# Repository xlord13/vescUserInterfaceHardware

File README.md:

# User interface board for VESC controller on e-twow scooter

This user interface board is based on an stm32F4 microcontroler.
The hardware design has been optimized for e-twow scooters, but can be adapted to any electric engine.
Is has been made with KiCad, which is a cross platform and open source electronics design automation suite.

This board communicates with a VESC controller by a UART interface.
It has 4 buttons and a color OLED 128x128 display (SSD1351) for user interaction.
Additionnaly, it includes 6 leds and a photo resistor for automatic lighting when ambient lighting is too low.

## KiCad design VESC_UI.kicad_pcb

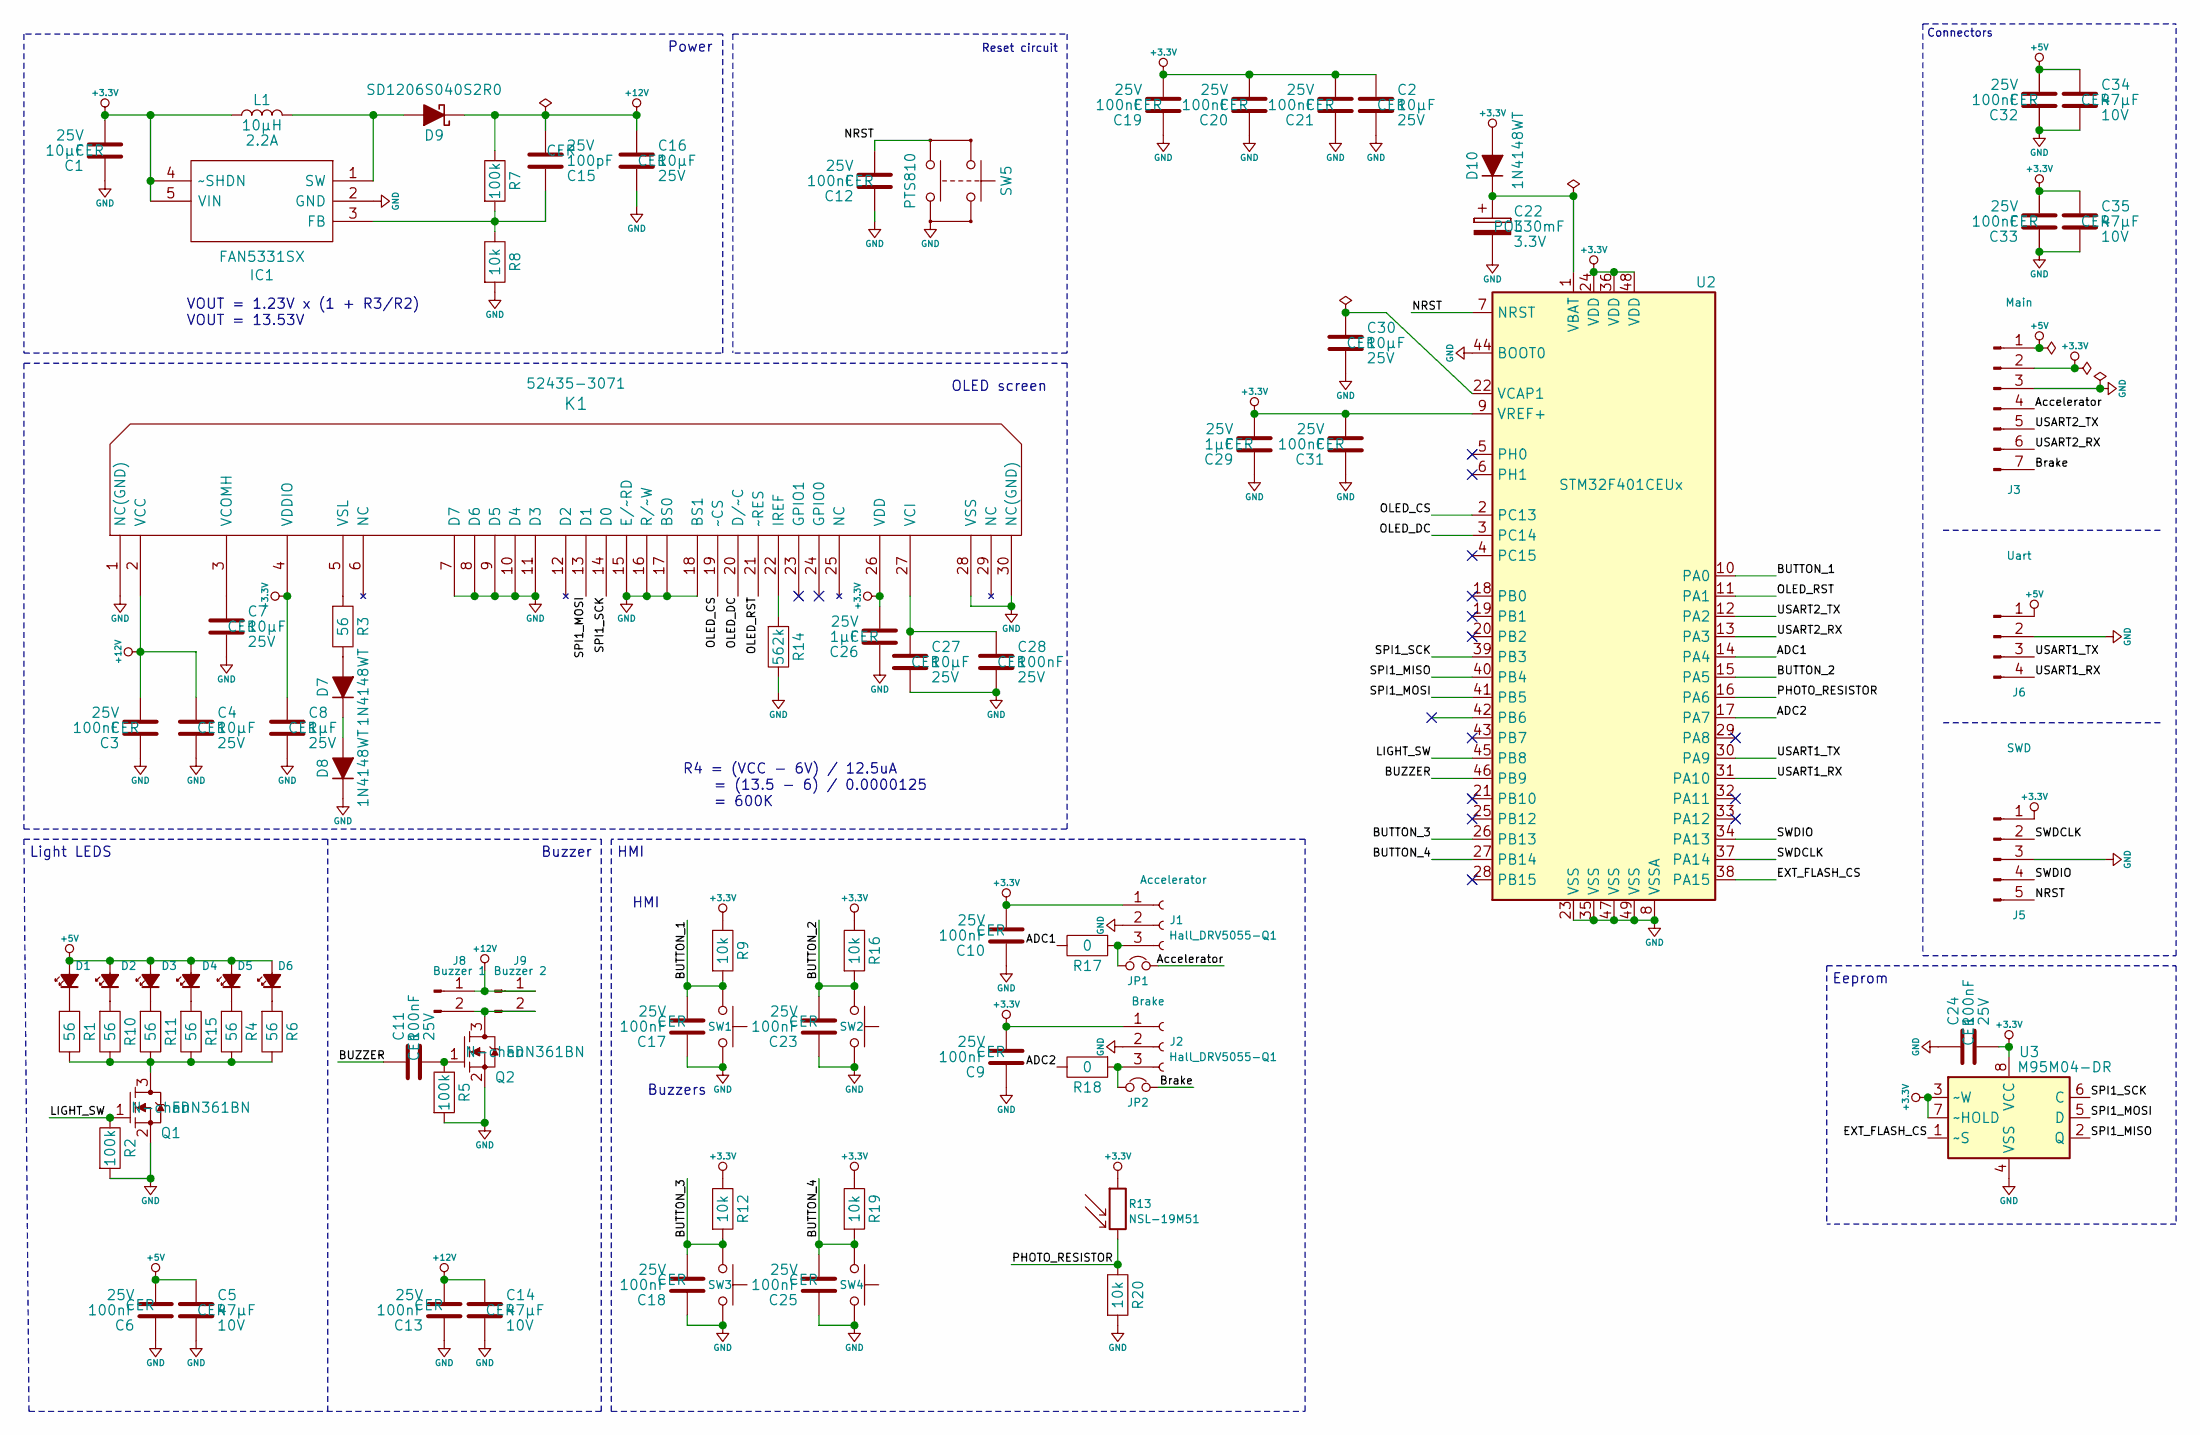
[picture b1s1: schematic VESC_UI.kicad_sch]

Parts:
C1, C2, C4, C7, C16, C27, C30: C_0003; C_0603
C3, C6, C9, C10, C11, C12, C13, C17, C18, C19, C20, C21, C23, C24, C25, C28, C31, C32, C33: C_0002; C_0402
C5, C14, C34, C35: C_0040; C_1210
C8, C26, C29: C_0037; C_0603
C15: C_0051; C_0402
C22: C_0046; CP_ELNA-DSK621
D1, D2, D3, D4, D5, D6: LED 5mm - White; LED_D5.0mm_Horizontal_O1.27mm_Z3.0mm_Clear
D7, D8, D10: D_0022; D_SOD-523-F
D9: D_0016; D_SOD-123
IC1: FAN5331SX; SOT95P280X145-5N; Mouser Part Number 512-FAN5331SX
J1, J2: Hall_DRV5055-Q1; TO-92Flat
J3: Conn_01x07_Male; JST_PH_B7B-PH-K_1x07_P2.00mm_Vertical
J5: Conn_01x05_Male; JST_PH_B5B-PH-K_1x05_P2.00mm_Vertical
J6: Conn_01x04_Male; JST_PH_B4B-PH-K_1x04_P2.00mm_Vertical
J8, J9: Conn_01x02_Male; JST_PH_B2B-PH-K_1x02_P2.00mm_Vertical
JP1, JP2: Jumper_NC_Small; SolderJumper-2_P1.3mm_Open_TrianglePad1.0x1.5mm
K1: K_0051-OBSOLETE; OLED128x128-1P5
L1: L_0006; L_4012-Wurth
Q1, Q2: Q_0020; SOT_23
R1, R4, R6, R10, R11, R15: R_0110; R_0603
R2, R5, R7: R_0034; R_0402
R3: R_0110; R_0402
R8, R9, R12, R16, R19, R20: R_0020; R_0402
R13: NSL-19M51; R_LDR_4.9x4.2mm_P2.54mm_Vertical
R14: R_0019; R_0402
R17, R18: R_0001; R_0402
SW1, SW2, SW3, SW4: Vertical push button; Vertical_push_button
SW5: SW_0003; PTS810
U2: STM32F401CEUx; QFN-48-1EP_7x7mm_P0.5mm_EP5.6x5.6mm
U3: M95M04-DR; SOIC-8_3.9x4.9mm_P1.27mm

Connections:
+3.3V: C1.2, C2.1, C8.1, C9.2, C10.2, C19.2, C20.2, C21.2, C24.2, C26.2, C29.2, C31.2, C33.2, C35.1, D10.2 (A), IC1.4 (~SHDN), IC1.5 (VIN), J1.1, J2.1, J3.2, J5.1, K1.4 (VDDIO), K1.26 (VDD), L1.2, R9.2, R12.2, R13.1, R16.2, R19.2, U2.9 (VREF+), U2.24 (VDD), U2.36 (VDD), U2.48 (VDD), U3.3 (~W), U3.7 (~HOLD), U3.8 (VCC)
+5V: C5.1, C6.2, C32.2, C34.1, D1.2 (A), D2.2 (A), D3.2 (A), D4.2 (A), D5.2 (A), D6.2 (A), J3.1, J6.1
+12V: C3.2, C4.1, C13.2, C14.1, C15.2, C16.1, D9.1 (K), J8.1, J9.1, K1.2 (VCC), R7.2
/ADC1: R17.2, U2.14 (PA4)
/ADC2: R18.2, U2.17 (PA7)
/Accelerator: J3.4, JP1.2
/BUTTON_1: C17.2, R9.1, SW1.1, U2.10 (PA0)
/BUTTON_2: C23.2, R16.1, SW2.1, U2.15 (PA5)
/BUTTON_3: C18.2, R12.1, SW3.1, U2.26 (PB13)
/BUTTON_4: C25.2, R19.1, SW4.1, U2.27 (PB14)
/BUZZER: C11.1, U2.46 (PB9)
/Brake: J3.7, JP2.2
/EXT_FLASH_CS: U2.38 (PA15), U3.1 (~S)
/LIGHT_SW: Q1.1 (G), R2.2, U2.45 (PB8)
/NRST: C12.2, J5.5, SW5.2, U2.7 (NRST)
/OLED_CS: K1.19 (~CS), U2.2 (PC13)
/OLED_DC: K1.20 (D/~C), U2.3 (PC14)
/OLED_RST: K1.21 (~RES), U2.11 (PA1)
/PHOTO_RESISTOR: R13.2, R20.2, U2.16 (PA6)
/SPI1_MISO: U2.40 (PB4), U3.2 (Q)
/SPI1_MOSI: K1.13 (D1), U2.41 (PB5), U3.5 (D)
/SPI1_SCK: K1.14 (D0), U2.39 (PB3), U3.6 (C)
/SWDCLK: J5.2, U2.37 (PA14)
/SWDIO: J5.4, U2.34 (PA13)
/USART1_RX: J6.4, U2.31 (PA10)
/USART1_TX: J6.3, U2.30 (PA9)
/USART2_RX: J3.6, U2.13 (PA3)
/USART2_TX: J3.5, U2.12 (PA2)
GND: C1.1, C2.2, C3.1, C4.2, C5.2, C6.1, C7.2, C8.2, C9.1, C10.1, C12.1, C13.1, C14.2, C16.2, C17.1, C18.1, C19.1, C20.1, C21.1, C22.2, C23.1, C24.1, C25.1, C26.1, C27.2, C28.2, C29.1, C30.2, C31.1, C32.1, C33.1, C34.2, C35.2, D8.1 (K), IC1.2 (GND), J1.2, J2.2, J3.3, J5.3, J6.2, K1.1 (NC(GND)), K1.7 (D7), K1.8 (D6), K1.9 (D5), K1.10 (D4), K1.11 (D3), K1.15 (E/~RD), K1.16 (R/~W), K1.17 (BS0), K1.18 (BS1), K1.28 (VSS), K1.30 (NC(GND)), Q1.2 (S), Q2.2 (S), R2.1, R5.1, R8.1, R14.2, R20.1, SW1.2, SW2.2, SW3.2, SW4.2, SW5.3, U2.8 (VSSA), U2.23 (VSS), U2.35 (VSS), U2.44 (BOOT0), U2.47 (VSS), U2.49 (VSS), U3.4 (VSS)
unnamed: C7.1, K1.3 (VCOMH)
unnamed: C11.2, Q2.1 (G), R5.2
unnamed: C15.1, IC1.3 (FB), R7.1, R8.2
unnamed: C22.1, D10.1 (K), U2.1 (VBAT)
unnamed: C27.1, C28.1, K1.27 (VCI)
unnamed: C30.1, U2.22 (VCAP1)
unnamed: D1.1 (K), R1.1
unnamed: D2.1 (K), R10.1
unnamed: D3.1 (K), R11.1
unnamed: D4.1 (K), R15.1
unnamed: D5.1 (K), R4.1
unnamed: D6.1 (K), R6.1
unnamed: D7.1 (K), D8.2 (A)
unnamed: D7.2 (A), R3.2
unnamed: D9.2 (A), IC1.1 (SW), L1.1
unnamed: J1.3, JP1.1, R17.1
unnamed: J2.3, JP2.1, R18.1
unnamed: J8.2, J9.2, Q2.3 (D)
unnamed: K1.5 (VSL), R3.1
unnamed: K1.22 (IREF), R14.1
unnamed: Q1.3 (D), R1.2, R4.2, R6.2, R10.2, R11.2, R15.2

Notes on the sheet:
Buzzer
HMI
Eeprom
Buzzers
Light LEDS
R4 = (VCC - 6V) / 12.5uA = (13.5 - 6) / 0.0000125 = 600K
Power
Connectors
Reset circuit
OLED screen
VOUT = 1.23V x (1 + R3/R2) VOUT = 13.53V

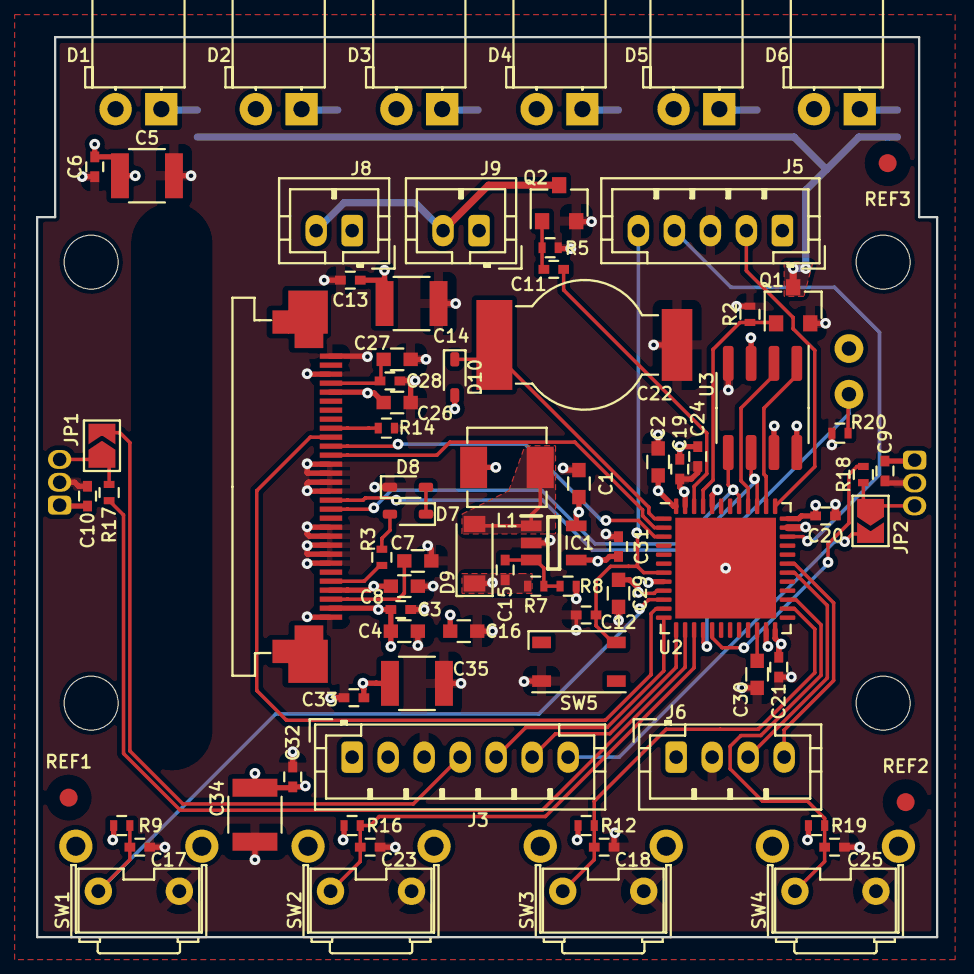
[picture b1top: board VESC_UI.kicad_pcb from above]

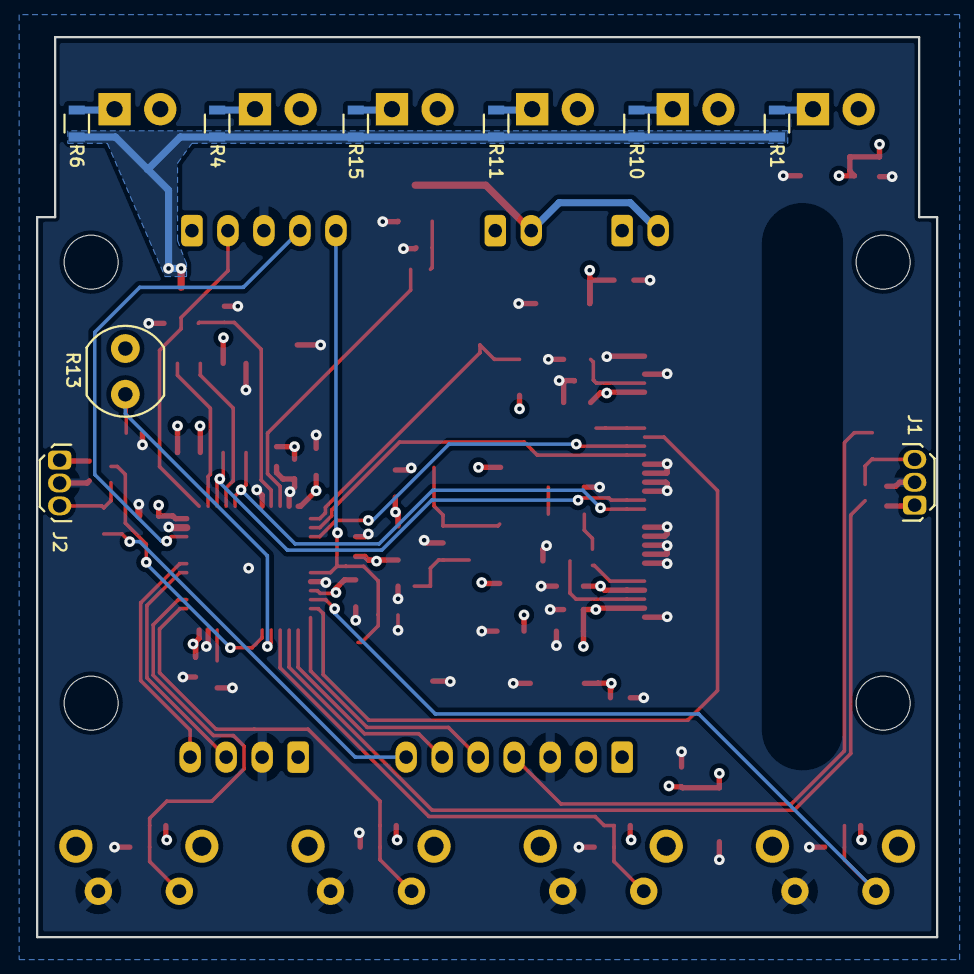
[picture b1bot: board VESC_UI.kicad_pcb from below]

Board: 4 copper layers, 50.0 x 50.0 mm, 93 parts (9 on the bottom side), 50 nets.

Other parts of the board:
Hole1, Hole2, Hole3, Hole4: MountingHole_3.2mm_M3_DIN965
REF1, REF2, REF3: CircleWhite1mm; REF_1mm

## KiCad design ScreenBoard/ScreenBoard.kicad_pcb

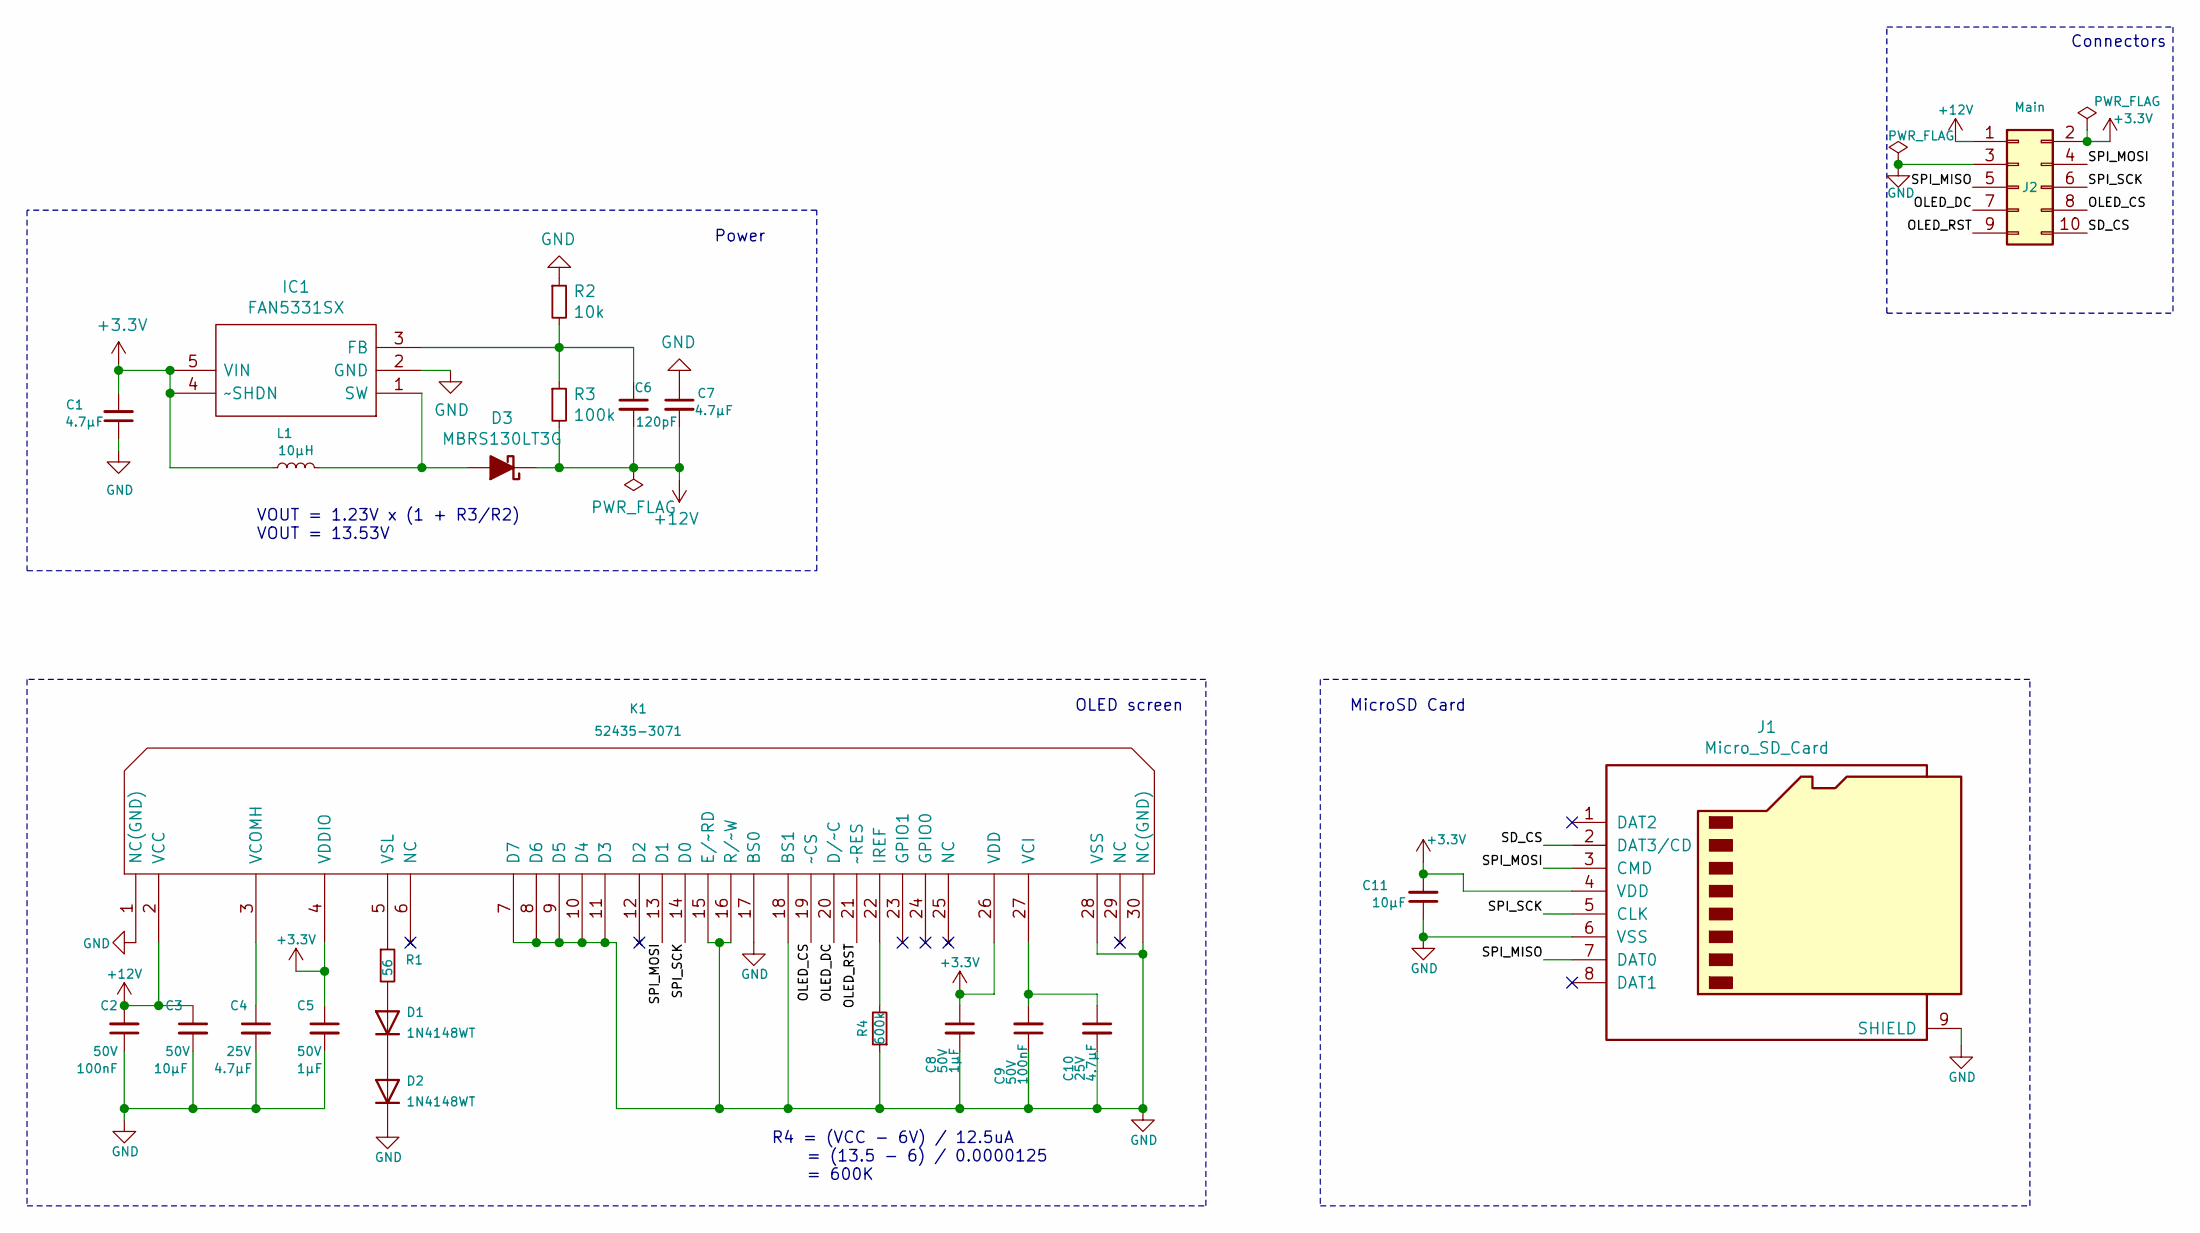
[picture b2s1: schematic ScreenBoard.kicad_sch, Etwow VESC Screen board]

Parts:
C1, C4, C7, C10: 4.7µF; C_0603_1608Metric_Pad1.05x0.95mm_HandSolder
C2, C9: 100nF; C_0603_1608Metric_Pad1.05x0.95mm_HandSolder
C3, C11: 10µF; C_1206_3216Metric_Pad1.42x1.75mm_HandSolder
C5, C8: 1µF; C_0805_2012Metric_Pad1.15x1.40mm_HandSolder
C6: 120pF; C_0603_1608Metric_Pad1.05x0.95mm_HandSolder
D1, D2: 1N4148WT; D_SOD-523
D3: MBRS130LT3G; D_SMB_Handsoldering
IC1: FAN5331SX; SOT95P280X145-5N; Mouser Part Number 512-FAN5331SX
J1: Micro_SD_Card; 693072010801
J2: Conn_02x05_Male; PinHeader_2x05_P2.00mm_Vertical_SMD
K1: OLED connector; 52435-3071
L1: 10µH; L_Coilcraft_LPS5030
R1: 56 Ohm; R_0603_1608Metric_Pad1.05x0.95mm_HandSolder
R2: 10k; R_0603_1608Metric_Pad1.05x0.95mm_HandSolder
R3: 100k; R_0603_1608Metric_Pad1.05x0.95mm_HandSolder
R4: 600k; R_0603_1608Metric_Pad1.05x0.95mm_HandSolder

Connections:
+3V3: C1.2, C5.1, C8.1, C11.2, IC1.4 (~SHDN), IC1.5 (VIN), J1.4 (VDD), J2.2, K1.4 (VDDIO), K1.26 (VDD), L1.1
+12V: C2.2, C3.1, C6.2, C7.2, D3.1 (K), J2.1, K1.2 (VCC), R3.2
/OLED_CS: J2.8, K1.19 (~CS)
/OLED_DC: J2.7, K1.20 (D/~C)
/OLED_RST: J2.9, K1.21 (~RES)
/SD_CS: J1.2 (DAT3/CD), J2.10
/SPI_MISO: J1.7 (DAT0), J2.5
/SPI_MOSI: J1.3 (CMD), J2.4, K1.13 (D1)
/SPI_SCK: J1.5 (CLK), J2.6, K1.14 (D0)
GND: C1.1, C2.1, C3.2, C4.2, C5.2, C7.1, C8.2, C9.1, C10.2, C11.1, D2.1 (K), IC1.2 (GND), J1.6 (VSS), J1.9 (SHIELD), J2.3, K1.1 (NC(GND)), K1.7 (D7), K1.8 (D6), K1.9 (D5), K1.10 (D4), K1.11 (D3), K1.15 (E/~RD), K1.16 (R/~W), K1.17 (BS0), K1.18 (BS1), K1.28 (VSS), K1.30 (NC(GND)), R2.1, R4.1
unnamed: C4.1, K1.3 (VCOMH)
unnamed: C6.1, IC1.3 (FB), R2.2, R3.1
unnamed: C9.2, C10.1, K1.27 (VCI)
unnamed: D1.1 (K), D2.2 (A)
unnamed: D1.2 (A), R1.2
unnamed: D3.2 (A), IC1.1 (SW), L1.2
unnamed: K1.5 (VSL), R1.1
unnamed: K1.22 (IREF), R4.2

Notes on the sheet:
VOUT = 1.23V x (1 + R3/R2) VOUT = 13.53V
Power
R4 = (VCC - 6V) / 12.5uA = (13.5 - 6) / 0.0000125 = 600K
OLED screen
MicroSD Card
Connectors

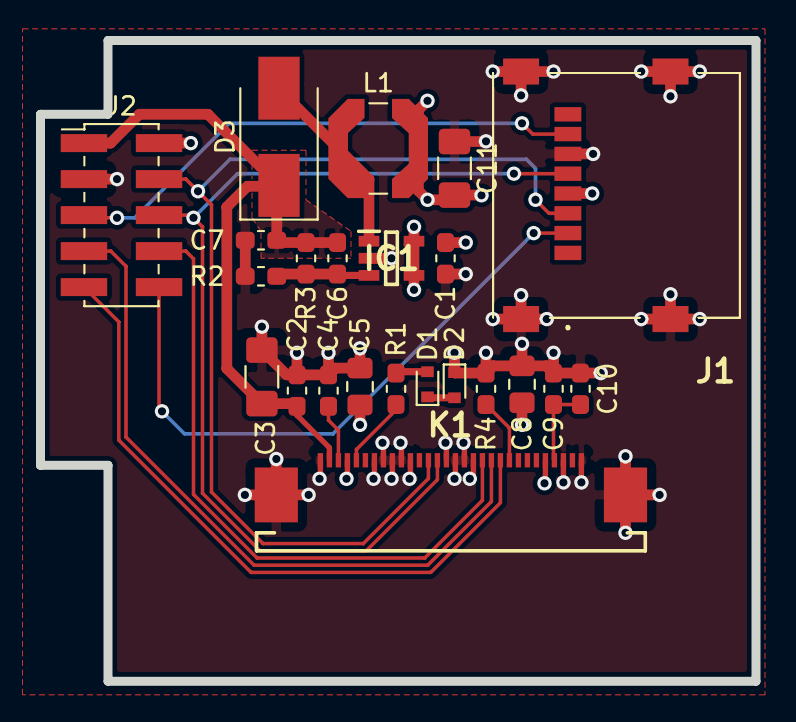
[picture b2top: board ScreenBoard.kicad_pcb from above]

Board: 4 copper layers, 39.8 x 35.6 mm, 23 parts (0 on the bottom side), 18 nets.

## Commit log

2020-10-05 Add KiCad project
2020-10-06 Modify crystal type
2020-10-21 Add RTC and buzzers
2020-12-12 first finished version
2020-12-12 fix: adjust LED 3d models
2020-12-12 Modify some areas
2020-12-14 fix: add missing rules and components
2020-12-17 fix: change screen connector footprint and adjust its mechanical position
2020-12-20 adjust vias drill dimension to comply PCB provider rules
2020-12-21 fix and refactor: both mainboard and screenboard
    Many improvements made
    - Fixed all issues with footprints
    - Optimized components placement and tracks
2020-12-24 Finalize new board
    - Remove some useless components
    - Change some footprints according to components availability
    - Optimize tracks and placements
    - Fix bad LDR and screen location
2020-12-25 feature: change power circuit
2020-12-27 Finalized PCBs
    - Add MicroSD Card support on screen board
    - Fix Hall sensors footprints (flip board side)
    - Change screen connector
2020-12-27 Add gerber fliles for production
2020-12-27 fix(screenBoard)
    - Wrong placement of some references on silkscreen layer
    - slightly adjust a track for homogeneity
2020-12-27 Change C11 footprint for better component availability
2020-12-27 update README file
2021-02-15 feature(screenBoard): add BOM and fix type on readme file
2021-03-05 fix(Mainboard): LEDs not working due to insufficient current
2021-07-20 Update to Kicad 6
2021-07-21 Update STM32 lib
2021-07-21 Generate PDF
2021-08-06 Route complete
2021-09-07 v2.0.0 version
2021-09-21 Update .pos files
2021-10-13 Update pos files
2021-11-22 Update project for placer
